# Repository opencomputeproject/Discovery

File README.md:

# Discovery
Work in progress for hardware rack discovery

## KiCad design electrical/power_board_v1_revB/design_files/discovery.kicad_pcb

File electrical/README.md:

#This part of the repo does contain electrical file for Discovery. All native files are created using KiCAD an opensource EDA tool which can be used to propose enhancement to the community. KiCAD works on Linux, Windows and MacOS

*You can find every version of the power board used for the Discovery. For every version you will have access to the design and production files folders

*Design files are used to design the board (schematic, routing etc).
In order to use them:
	-Download every files
	-Copy them in a folder
	-Open the .pro file with Kicad.
You will then have access to the different design part of the project

*Production file folder contains every files needed to product the board (gerber, drill, BOM etc)

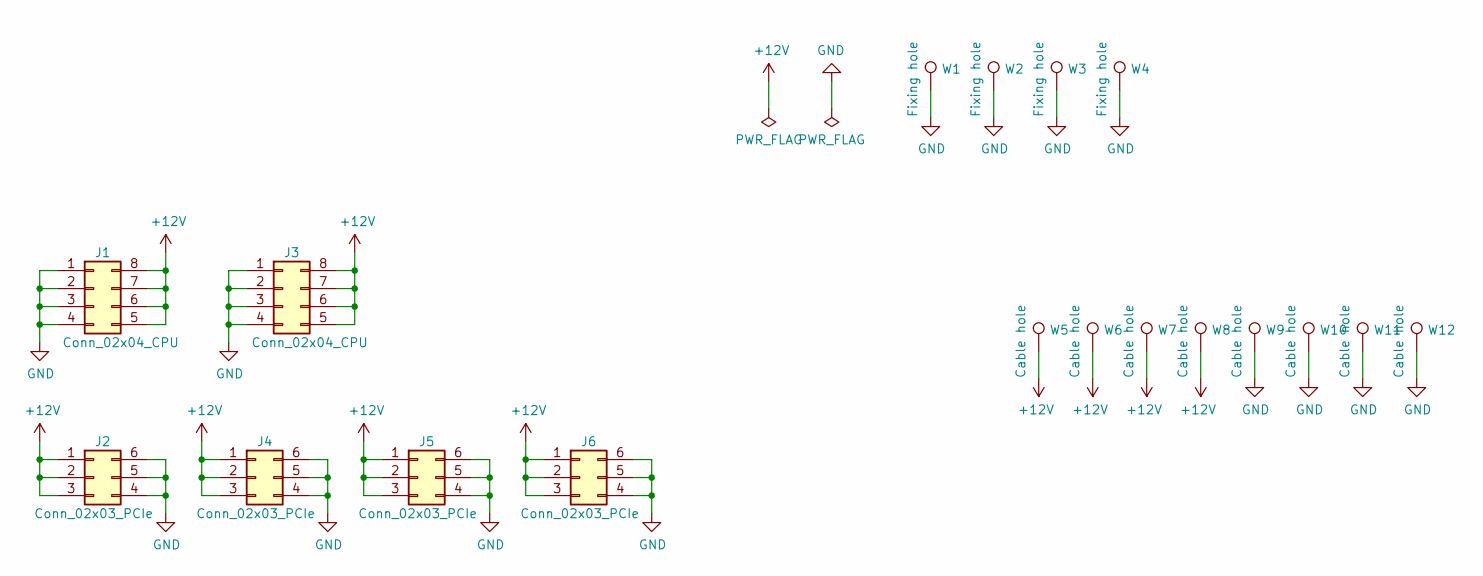
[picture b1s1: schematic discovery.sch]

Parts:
J1, J3: Conn_02x04_CPU; CONN_02x04_4.2mm
J2, J4, J5, J6: Conn_02x03_PCIe; CONN_02x03_4.2mm
W1, W2, W3, W4: Fixing hole; FixingPoint_Plated_Hole_D4.0mm
W5, W6, W7, W8, W9, W10, W11, W12: Cable hole; fixing_hole

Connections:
+12V: J1.5, J1.6, J1.7, J1.8, J2.1, J2.2, J2.3, J3.5, J3.6, J3.7, J3.8, J4.1, J4.2, J4.3, J5.1, J5.2, J5.3, J6.1, J6.2, J6.3, W5.1, W6.1, W7.1, W8.1
GND: J1.1, J1.2, J1.3, J1.4, J2.4, J2.5, J2.6, J3.1, J3.2, J3.3, J3.4, J4.4, J4.5, J4.6, J5.4, J5.5, J5.6, J6.4, J6.5, J6.6, W1.1, W2.1, W3.1, W4.1, W9.1, W10.1, W11.1, W12.1

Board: 2 copper layers, 18 parts (0 on the bottom side), 2 nets, no tracks yet.

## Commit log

2019-03-28 Add initial files to the repo as well as directory structure
2019-04-05 Create doc cable version
2019-04-05 Create prod discovery v2.zip
    Production files for the discovery board, cable version
2019-04-05 Discovery board - cable version
    In this folder you have all of the design files of the PCB, production files for the PCB and a documentation for the board
2019-04-08 Modification Discovery
    I deleted the ZIP and RAR files and created sub directories which contain all the files and renamed the doc with an .md extension
2019-04-09 Update
    I deleted the bak files to have a cleaner folder and made the .md files with more markdown formatting
2019-04-10 Improvement
    PCI connectors on the board have been modified into 2x3pins (2x4 pins originally).
    Design and production files have been updated
2019-04-15 First mechanical files publication
2019-04-15 Adding BOM
2019-04-16 Add initial licensing requirement
2019-04-16 Add initial contributors list
2019-04-18 Add intro pictures of Discovery chassis concept
2019-04-18 es picture rendering on landing page
2019-04-18 Fix the picture raw path
